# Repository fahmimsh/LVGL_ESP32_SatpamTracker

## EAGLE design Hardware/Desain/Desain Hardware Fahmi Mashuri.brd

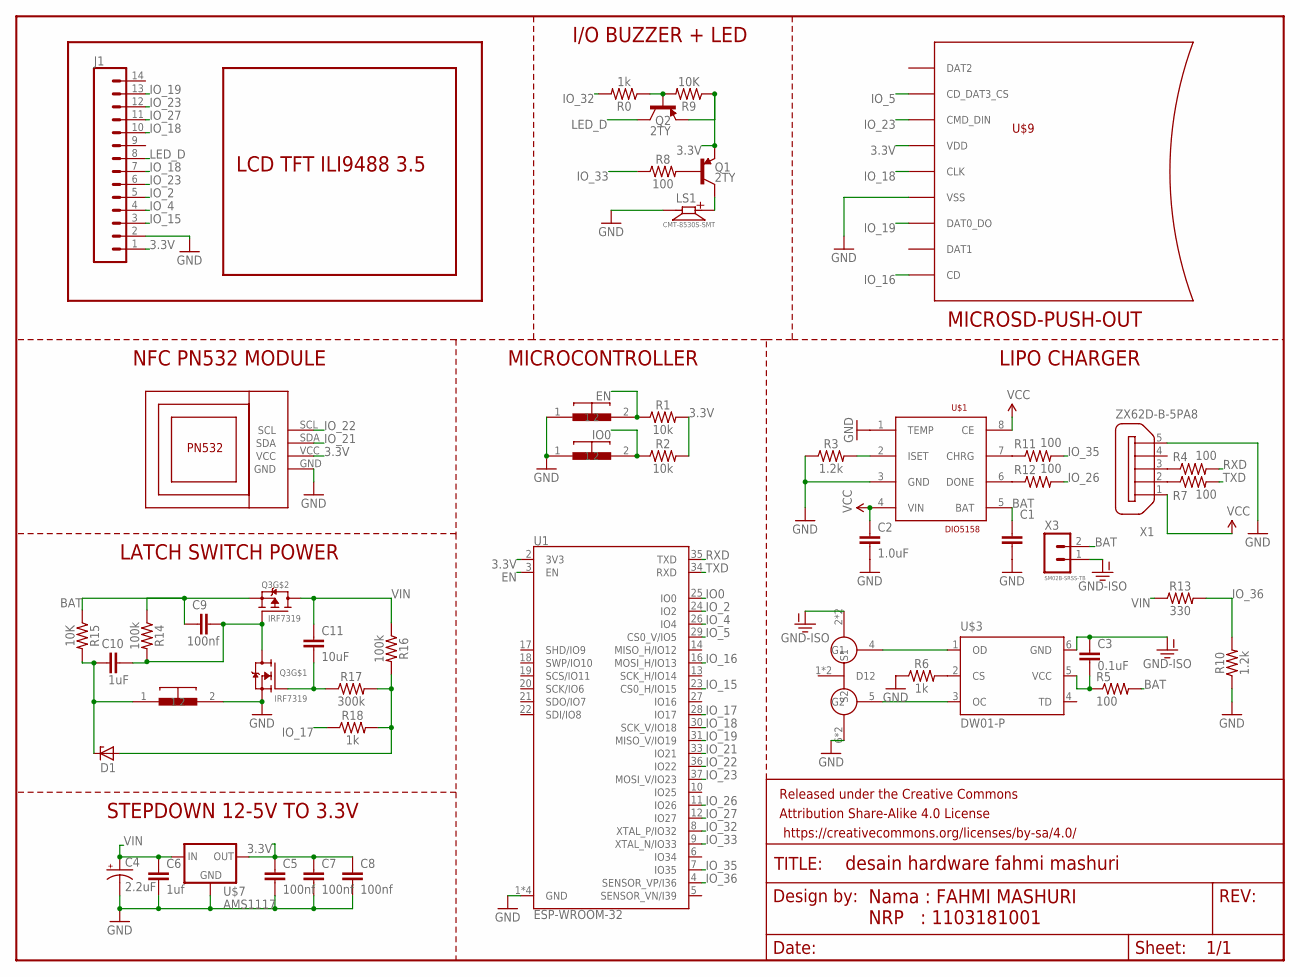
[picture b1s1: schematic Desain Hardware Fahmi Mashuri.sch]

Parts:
C1: 10uF; C0805K
C2: 1.0uF; 0603
C3: 0.1uF; 0603
C4: 2.2uF; EIA3528
C5, C7, C8, C9: 100nf; C0603K
C6: 1uf; C0805K
C10: 1uF; C0603K
C11: 10uF; C0603K
D1: ZENER-DIODE-SOD-323; SOD-323
FRAME1: FRAME-LETTER; CREATIVE_COMMONS
J1: CONN_14; 1X14
LS1: CMT-8530S-SMT; CUI_CMT-8530S-SMT
Q1, Q2: 2TY; SOT23-3
Q3: IRF7319; SOIC127P600X175-8N
R0, R6, R18: 1k; 0603
R1, R2: 10k; 0603
R3, R10: 1.2k; 0603
R4, R7, R8, R11, R12: 100; 0603
R5: 100; 0603-RES
R9, R15: 10K; 0603
R13: 330; 0603
R14, R16: 100k; 0603
R17: 300k; 0603
U1: ESP-WROOM-32
U$1: DIO5158; SOIC-8
U$2: PN532_NFC
U$3: DW01-P; SOT23-6L
U$4: FS8205A; TSSOP8
U$5, U$6, U$8: PUSHBUTTOMICRO
U$7: AMS1117; SOT223
U$9: MICROSD-PUSH-OUT
X1: ZX62D-B-5PA8
X3: SM02B-SRSS-TB

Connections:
3.3V: C5.1, C7.1, C8.1, J1.1, Q1.2 (E), Q2.2 (E), R1.2, R2.2, R9.1, U1.2 (3V3), U$2.VCC, U$7.2 (OUT), U$9.4 (VDD)
BAT: C1.1, C9.1, Q3.3 (S2), R5.2, R14.1, R15.1, U$1.5 (BAT), X3.2
EN: R1.1, U1.3 (EN), U$5.2
GND: C1.2, C2.2, C4.C (-), C5.2, C6.2, C7.2, C8.2, J1.2, LS1.N, Q3.1 (S1), R3.1, R6.1, R10.1, U1.1 (GND), U1.15 (GND), U1.38 (GND), U1.GND, U$1.1 (TEMP), U$1.3 (GND), U$2.GND, U$4.6 (S2), U$4.7 (S2), U$5.1, U$6.1, U$7.1 (GND), U$8.2, U$9.6 (VSS), U$9.G1 (VSS), U$9.G2 (VSS), U$9.G3 (VSS), U$9.G4 (VSS), X1.5
GND-ISO: C3.1, U$3.6 (GND), U$4.2 (S1), U$4.3 (S1), X3.1
IO0: R2.1, U1.25 (IO0), U$6.2
IO_2: J1.5, U1.24 (IO2)
IO_4: J1.4, U1.26 (IO4)
IO_5: U1.29 (CS0_V/IO5), U$9.2 (CD_DAT3_CS)
IO_15: J1.3, U1.23 (CS0_H/IO15)
IO_16: U1.16 (MOSI_H/IO13), U$9.CD
IO_17: R18.1, U1.28 (IO17)
IO_18: J1.7, J1.10, U1.30 (SCK_V/IO18), U$9.5 (CLK)
IO_19: J1.13, U1.31 (MISO_V/IO19), U$9.7 (DAT0_DO)
IO_21: U1.33 (IO21), U$2.SDA
IO_22: U1.36 (IO22), U$2.SCL
IO_23: J1.6, J1.12, U1.37 (MOSI_V/IO23), U$9.3 (CMD_DIN)
IO_26: R12.2, U1.11 (IO26)
IO_27: J1.11, U1.12 (IO27)
IO_32: R0.2, U1.8 (XTAL_P/IO32)
IO_33: R8.1, U1.9 (XTAL_N/IO33)
IO_35: R11.2, U1.7 (IO35)
IO_36: R10.2, R13.2, U1.4 (SENSOR_VP/I36)
LED_D: J1.8, Q2.3 (C)
unnamed: R6.2, U$3.2 (CS)
unnamed: U$3.3 (OC), U$4.5 (G2)
unnamed: R3.2, U$1.2 (ISET)
unnamed: U$3.1 (OD), U$4.4 (G1)
unnamed: R4.1, X1.3
unnamed: R7.1, X1.2
unnamed: LS1.P, Q1.3 (C)
unnamed: Q1.1 (B), R8.2
unnamed: Q2.1 (B), R0.1, R9.2
unnamed: R11.1, U$1.7 (CHRG)
unnamed: R12.1, U$1.6 (DONE)
unnamed: D1.A, R16.2, R17.2, R18.2
unnamed: C11.2, Q3.2 (G1), R17.1
unnamed: C9.2, C10.2, Q3.4 (G2), Q3.7 (D1), Q3.8 (D1), R14.2
unnamed: C10.1, D1.C, R15.2, U$8.1
RXD: R4.2, U1.35 (TXD)
TXD: R7.2, U1.34 (RXD)
VCC: C2.1, U$1.4 (VIN), U$1.8 (CE), X1.1
VCC-DW: C3.2, R5.1, U$3.5 (VCC)
VIN: C4.A (+), C6.1, C11.1, Q3.5 (D2), Q3.6 (D2), R13.1, R16.1, U$7.3 (IN)

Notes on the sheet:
LIPO CHARGER
MICROCONTROLLER
STEPDOWN 12-5V TO 3.3V
LATCH SWITCH POWER
NFC PN532 MODULE
LCD TFT ILI9488 3.5
I/O BUZZER + LED

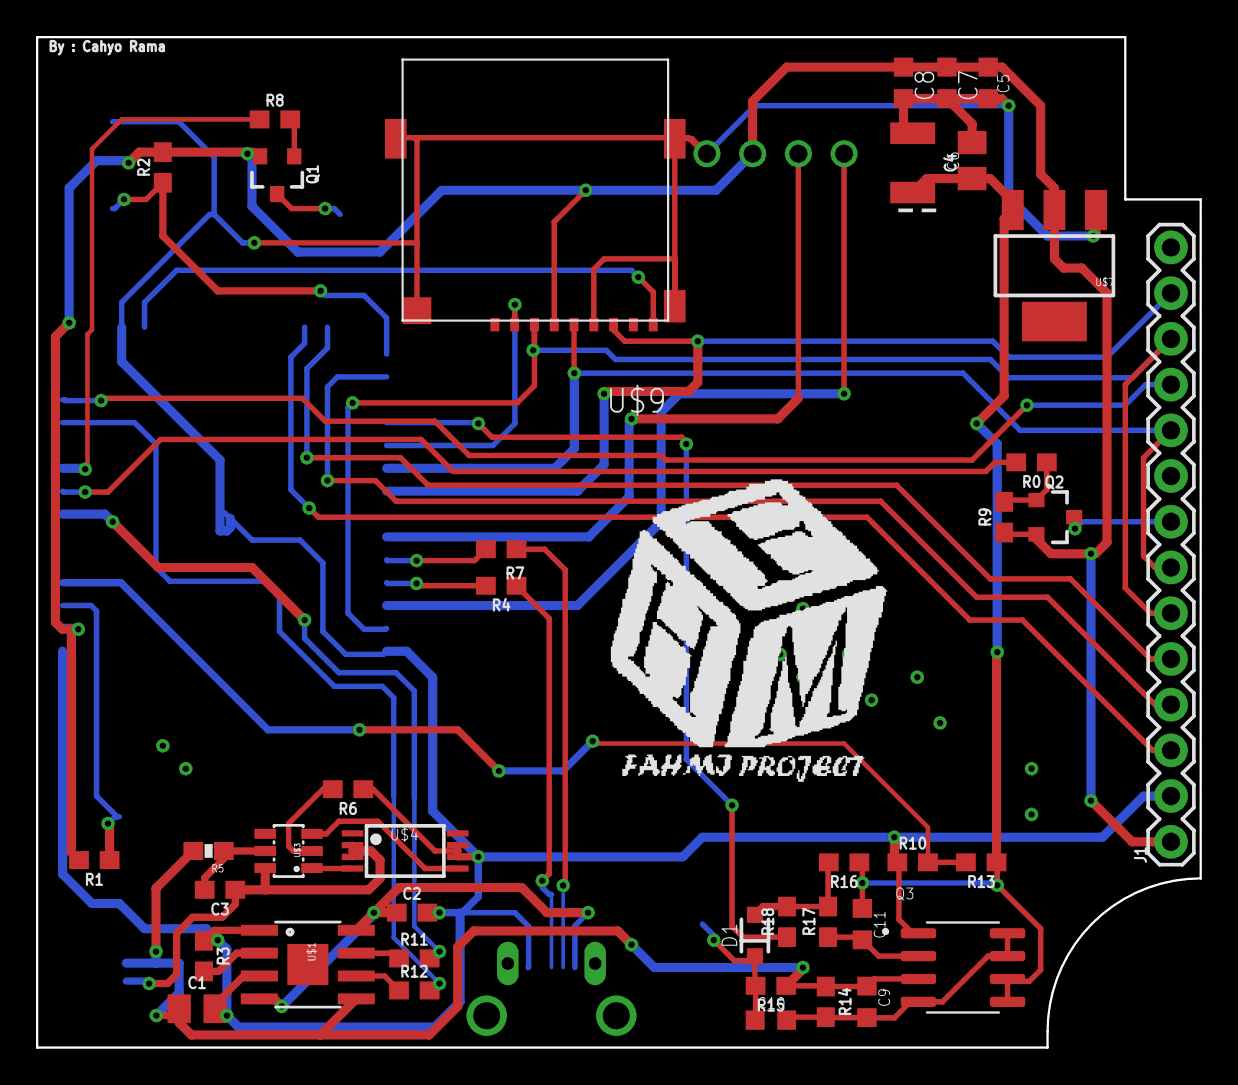
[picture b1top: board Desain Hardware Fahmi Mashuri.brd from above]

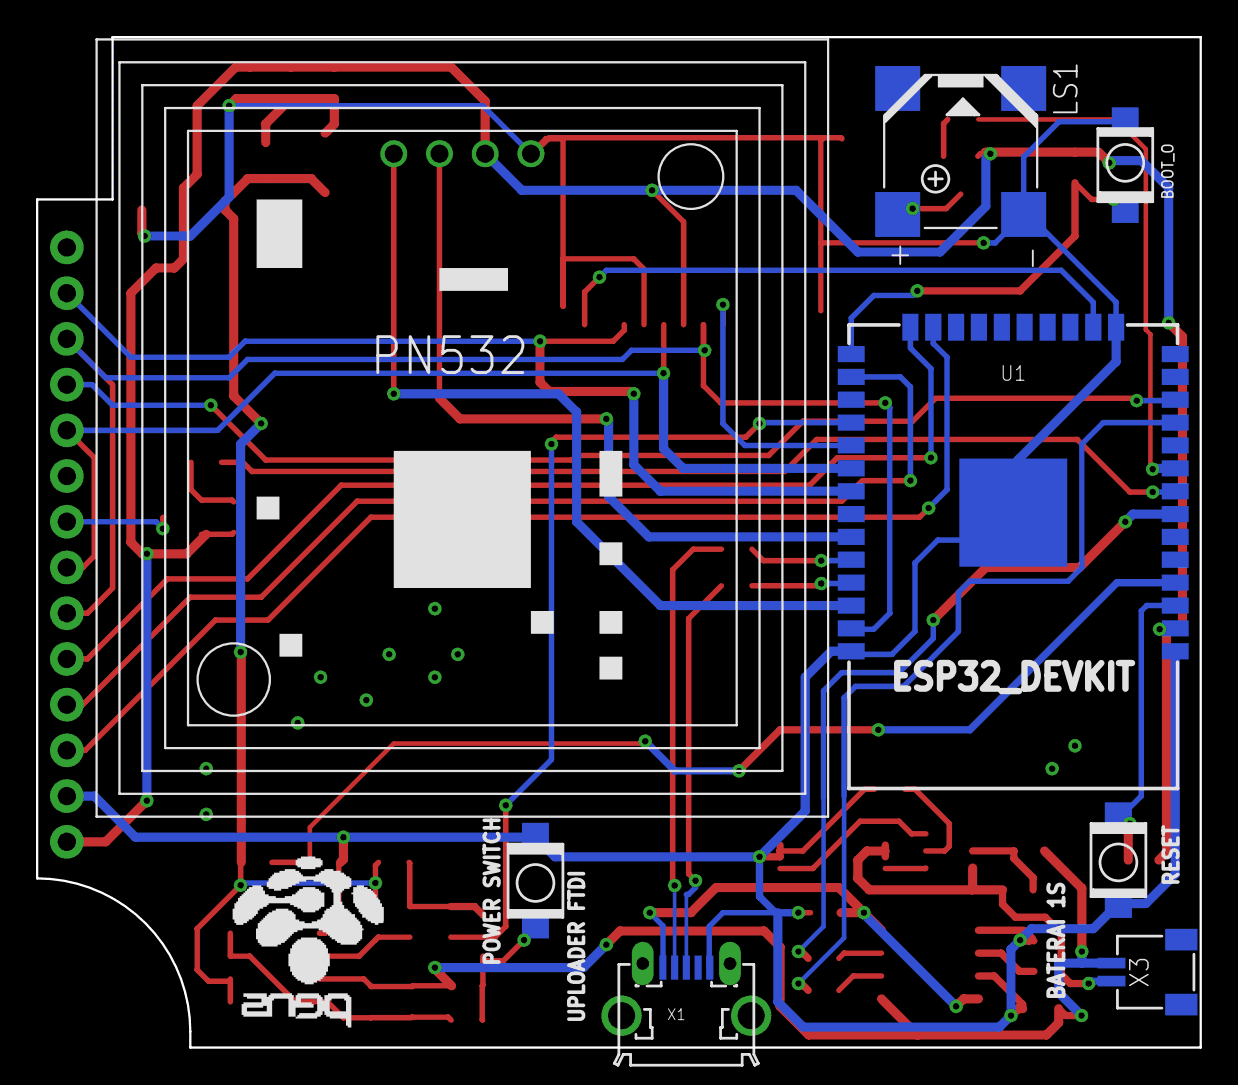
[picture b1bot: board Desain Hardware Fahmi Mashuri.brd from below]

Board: 2 copper layers, 64.6 x 56.1 mm, 49 parts (8 on the bottom side), 44 nets.

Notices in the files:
parts and their libraries:
SparkFun-Capacitors: Licensing: Creative Commons ShareAlike 4.0 International - https://creativecommons.org/licenses/by-sa/4.0
SparkFun: Licensing: CC v3.0 Share-Alike You are welcome to use this library for commercial purposes.
SparkFun-Aesthetics: https://creativecommons.org/licenses/by-sa/4.0
